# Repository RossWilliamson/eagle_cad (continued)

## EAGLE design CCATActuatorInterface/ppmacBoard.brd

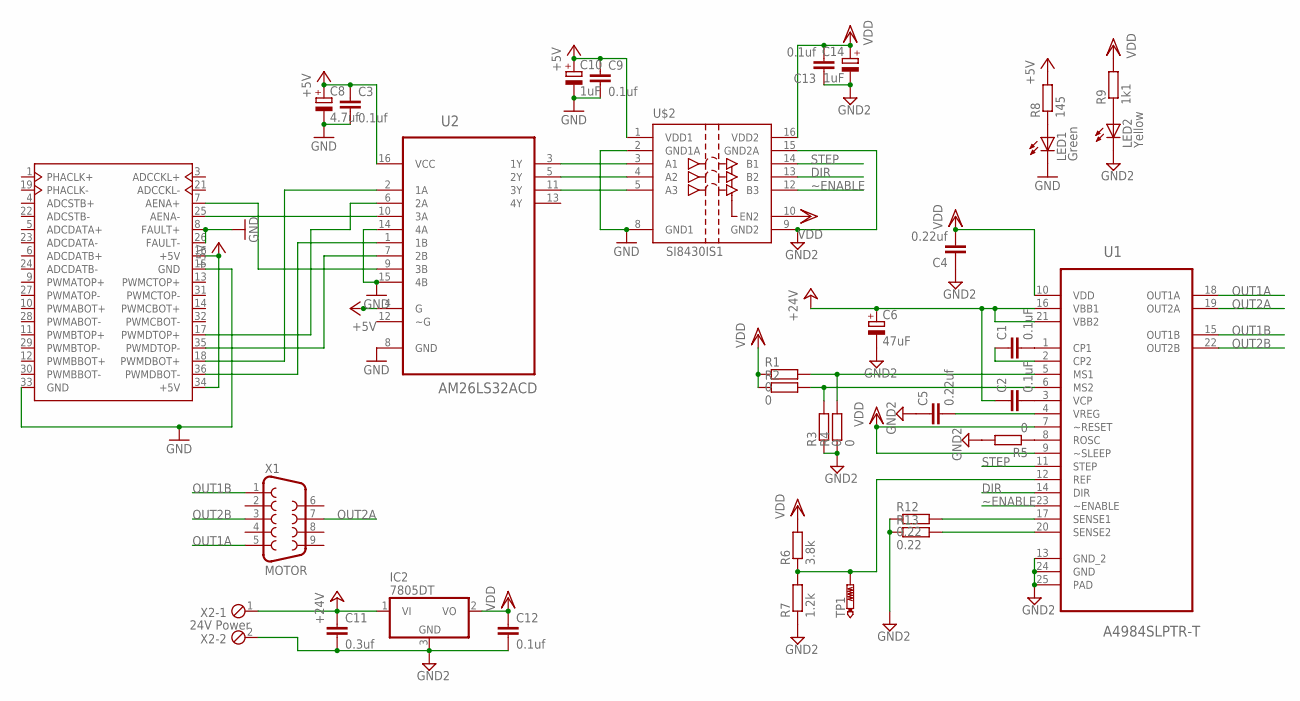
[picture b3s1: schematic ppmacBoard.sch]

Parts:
C1, C2: 0.1uF; C1206; MPN MC1206B104K250CT
C3, C9, C12, C13: 0.1uf; C1206; PARTNO C1206C104K3RACTU
C4, C5: 0.22uf; C1206; PARTNO C1206C224K5RACTU
C6: 47uF; E7,5-18; PARTNO ESH476M035AE3AA
C8: 4.7uf; A/3216-18W; PARTNO T491A475M025AT
C10, C14: 1uF; A/3216-18W; PARTNO T491A105K025AT
C11: 0.3uf; C1206; PARTNO C3216X7R1E334K
IC2: 7805DT; TO252; PARTNO BA17805FP-E2
LED1: Green; 1206; MPN KP-3216CGCK
LED2: Yellow; 1206; MPN KP-3216SYCK
R1, R2, R3, R4, R5: 0; R1206; PARTNO RMCF1206ZT0R00
R6: 3.8k; R1206; PARTNO RMCF1206FT3K83
R7: 1.2k; R1206; PARTNO RC1206FR-071K2L
R8: 145; R1206; PARTNO RC1206FR-07140RL
R9: 1k1; R1206; PARTNO RC1206FR-071K1L
R12, R13: 0.22; R2010; PARTNO WSLT2010R2200FEB18
TP1: PTR1PAD1-13; P1-13
U1: A4984SLPTR-T; SOP65P640X120-24N; PARTNO A4984SLPTR-T
U2: AM26LS32ACD; SOIC127P600X175-16N; PARTNO AM26LS32ACDR
U$1: DIGAMPOUT_PCB; 3M_10136-52B2PC_PCB; PARTNO 10136-3000PE
U$2: SI8430IS1; SO16; PARTNO SI8430AB-D-IS1
X1: MOTOR; F09H; PARTNO DLS1XS5AK40X
X2: 24V Power; 2POL254; PARTNO OSTTE020104

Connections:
+5V: C3.1, C8.+, C9.1, C10.+, R8.2, U2.4 (G), U2.16 (VCC), U$1.16 (+5V), U$1.34 (+5V), U$2.1 (VDD1)
+24V: C2.1, C6.+, C11.1, IC2.1 (VI), U1.16 (VBB1), U1.21 (VBB2), X2.1
DIR: U1.14 (DIR), U$2.13 (B2)
GND: C3.2, C8.-, C9.2, C10.-, LED1.C, U2.8 (GND), U2.14 (4A), U2.15 (4B), U$1.8 (FAULT+), U$1.15 (GND), U$1.26 (FAULT-), U$1.33 (GND), U$2.2 (GND1A), U$2.8 (GND1)
GND2: C4.1, C5.1, C6.-, C11.2, C12.2, C13.1, C14.-, IC2.3 (GND), LED2.C, R3.1, R4.1, R5.2, R7.1, R12.1, R13.1, U1.13 (GND_2), U1.24 (GND), U1.25 (PAD), U$2.9 (GND2), U$2.15 (GND2A), X2.2
unnamed: R2.2, R3.2, U1.6 (MS2)
unnamed: R1.2, R4.2, U1.5 (MS1)
unnamed: C1.2, U1.1 (CP1)
unnamed: C2.2, U1.3 (VCP)
unnamed: C1.1, U1.2 (CP2)
unnamed: LED1.A, R8.1
unnamed: R12.2, U1.17 (SENSE1)
unnamed: R6.1, R7.2, TP1.TP, U1.12 (REF)
unnamed: C5.2, U1.4 (VREG)
unnamed: R5.1, U1.8 (ROSC)
unnamed: U2.10 (3A), U$1.25 (AENA-)
unnamed: U2.9 (3B), U$1.7 (AENA+)
unnamed: U2.2 (1A), U$1.18 (PWMDBOT+)
unnamed: U2.1 (1B), U$1.36 (PWMDBOT-)
unnamed: U2.7 (2B), U$1.35 (PWMDTOP-)
unnamed: U2.6 (2A), U$1.17 (PWMDTOP+)
unnamed: U2.3 (1Y), U$2.3 (A1)
unnamed: U2.5 (2Y), U$2.4 (A2)
unnamed: U2.11 (3Y), U$2.5 (A3)
unnamed: LED2.A, R9.1
unnamed: R13.2, U1.20 (SENSE2)
OUT1A: U1.18 (OUT1A), X1.5
OUT1B: U1.15 (OUT1B), X1.1
OUT2A: U1.19 (OUT2A), X1.7
OUT2B: U1.22 (OUT2B), X1.3
STEP: U1.11 (STEP), U$2.14 (B1)
VDD: C4.2, C12.1, C13.2, C14.+, IC2.2 (VO), R1.1, R2.1, R6.2, R9.2, U1.7 (~RESET), U1.9 (~SLEEP), U1.10 (VDD), U$2.10 (EN2), U$2.16 (VDD2)
~ENABLE: U1.23 (~ENABLE), U$2.12 (B3)

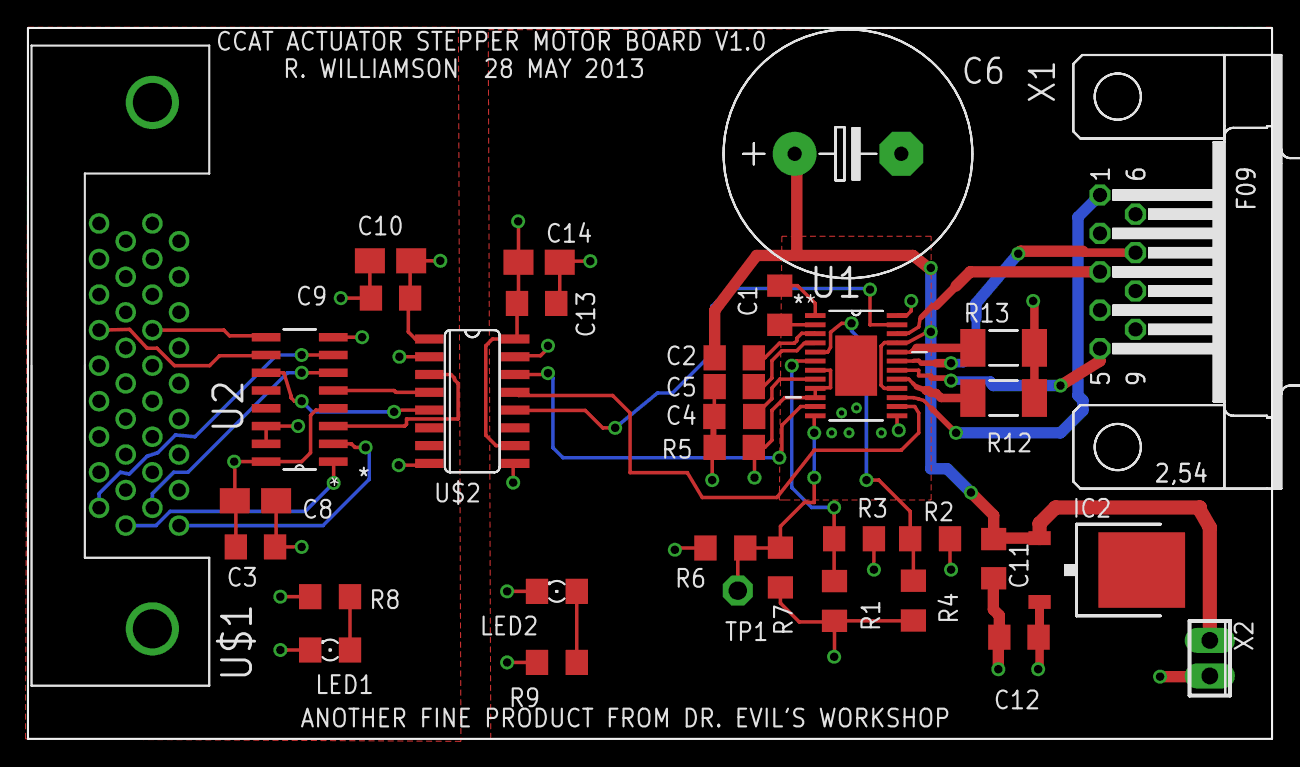
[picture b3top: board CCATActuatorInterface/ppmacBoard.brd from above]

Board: 4 copper layers, 88.9 x 50.8 mm, 34 parts (0 on the bottom side), 33 nets.

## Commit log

2013-12-20 First commit of eaglecad boards
